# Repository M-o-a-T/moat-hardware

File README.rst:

=============
MoaT Hardware
=============

This is the collection of files for the physical side of MoaT:
Schematics and layouts (kicad), Enclosures (OpenSCAD).

++++++++++++++++
Up-to-date stuff
++++++++++++++++

---
BMS
---

Controller and module for battery management.

The hardware design supports both active-high (diyBMS) and active-low
(MoaT) serial connections.

----
Wire
----

Connect some wires to the MoaT board.

----
misc
----

Random stuff (Enocean adapter, USB intercept, …).

-----
adapt
-----

+++++++++
Old stuff
+++++++++

CPUs
====

The ``proc/`` directory contains CPU boards, i.e. things that have a bus plug.

CPUs are responsible for adapting 1wire (5V) and MoaTbus (12V) to their
internal voltage.

Boards
======

The ``board/`` directory contains everything that has a bus socket, i.e.
interfaces to the Real World.

Many of these boards have 12V-MoaTbus, 5V-1wire, and/or 3.3V-I2C connectors.

The boards are not responsible for translating voltages to the (commonly)
3.3V which CPUs expect.

Breadboard
++++++++++

The most important part. Use this to test CPUs.

Heating
+++++++

This board has two transistors to switch one or two 24V radiator
valves (PPM).

Smoke detector
++++++++++++++

This board fits into a Gira Dual or Q smoke detector.

Old stuff
=========

The ``old/`` directory contains things I need to clean up.

+++++++++
Licensing
+++++++++

(Almost) all files in this archive are (c) 2021-2022 by Matthias Urlichs.
They are licensed under the GNU General Public License, V3.

This means: if you use any these files to build something which you sell or
give to somebody else, you're required to make the schematics, layouts,
design files, and source code of the resulting product available.

Developing these devices takes time and money. Thus, while using all or
part of this achive commercially is OK, their creators hereby humbly ask
for adequate financial remuneration if you use any of these files for
monetary gain. Thank you.

License exception
+++++++++++++++++

The battery module in the bms/cell subdirectory has originally been
designed by Stuart Pittaway. It is governed by a Creative Commons
Attribution-NonCommercial-ShareAlike 2.0 UK: England/Wales license. See the
file ``bms/cell/LICENSE`` for details.

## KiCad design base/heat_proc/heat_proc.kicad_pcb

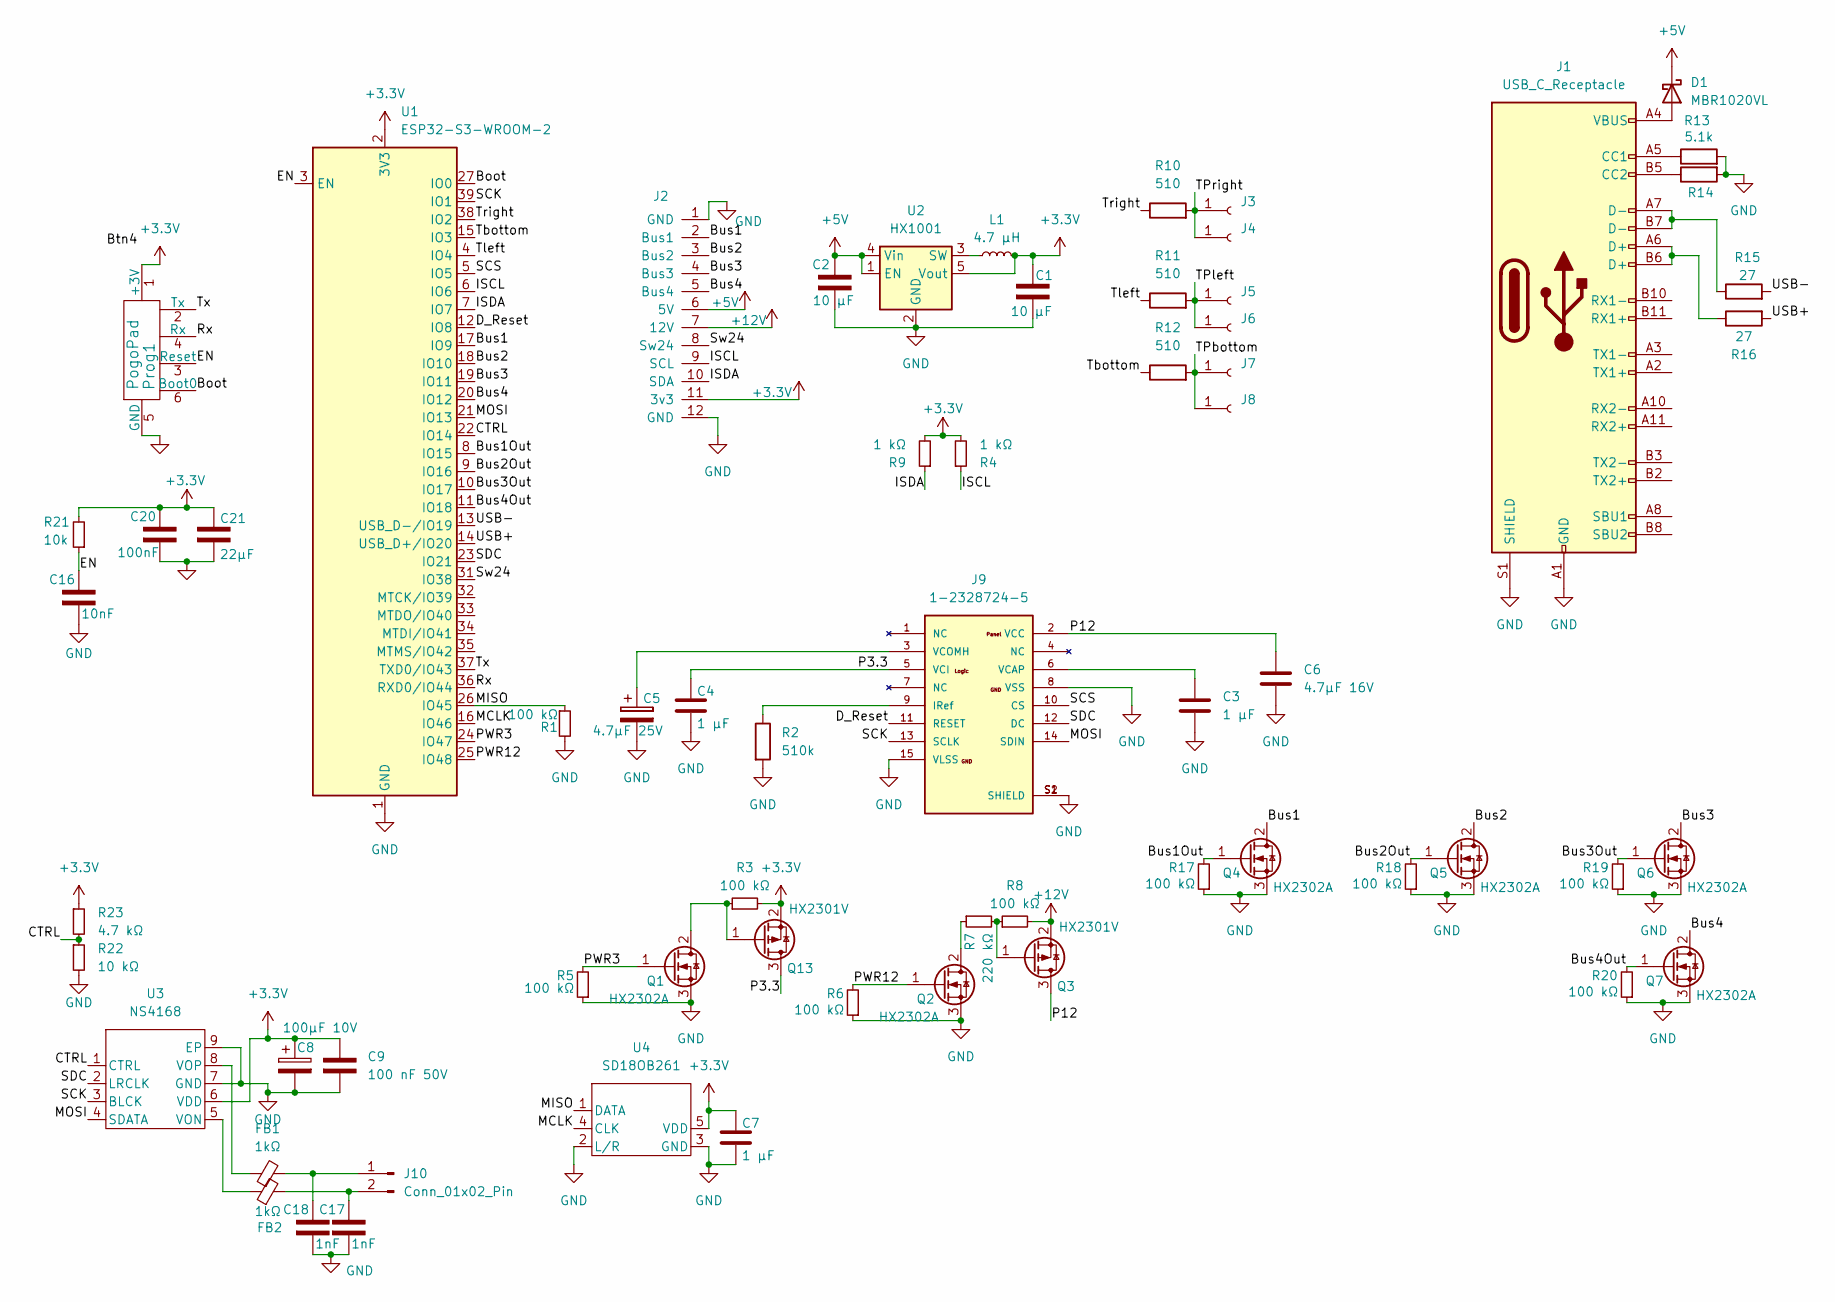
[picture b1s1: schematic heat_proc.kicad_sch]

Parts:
C1, C2: CP_10µ_16V_0603; C_0603_1608Metric; LCSC C108340
C3, C4, C7: C_1µ_25V_0603; C_0603_1608Metric; Farnell 3581460
C5: 4.7µF 25V; C_0603_1608Metric; LCSC C69335
C6: 4.7µF 16V; C_0603_1608Metric; LCSC C69335
C8: CP_100µ_10V; C_1210_3225Metric; Farnell 2326221
C9: CP_100n_50V_0603; C_0603_1608Metric; LCSC C14663
C16: 10nF; C_0603_1608Metric; LCSC C1589
C17, C18: 1nF; C_0603_1608Metric; LCSC C1588
C20: 100nF; C_0402_1005Metric; LCSC C6119799
C21: 22µF; C_1206_3216Metric; LCSC C12891
D1: MBR1020VL; D_SOD-123; LCSC C6299858
FB1, FB2: 1kΩ; L_0805_2012Metric; LCSC C51018431
J1: USB_C_Receptacle; USB_C_Receptacle_GCT_USB4110; LCSC C5143397
J2: Moat_Heat_12; JST_SH_SM12B-SRSS-TB_1x12-1MP_P1.00mm_Horizontal; MPN SM12B-SRSS-TB; LCSC C160411
J3, J4, J5, J6, J7, J8: Conn_01x01_Socket; SolderWire-0.5sqmm_1x01_D0.9mm_OD2.1mm
J9: 1-2328724-5; OLED96; LCSC C2919525
J10: Conn_01x02_Pin; Fuse_1210_3225Metric_Pad1.42x2.65mm_HandSolder
L1: 4.7 µH; L_0603_1608Metric; LCSC C295681
Prog1: PogoPad; 2X3_PAD; LCSC C2685197
Q1, Q2, Q4, Q5, Q6, Q7: HX2302A; SOT-23; LCSC C296295
Q3, Q13: HX2301V; SOT-23; LCSC C7499856
R1, R3, R5, R6, R8, R17, R18, R19, R20: R_100k_0603; R_0603_1608Metric; LCSC C14675
R2: 510k; R_0603_1608Metric; LCSC C23192
R4, R9: R_1k_0603; R_0603_1608Metric; LCSC C21190
R7: R_220k_0603; R_0603_1608Metric; LCSC C22961
R10, R11, R12: 510; R_0603_1608Metric; LCSC C23193
R13, R14: 5.1k; R_0603_1608Metric; LCSC C23186
R15, R16: 27; R_0402_1005Metric; LCSC C321419
R21: 10k; R_0603_1608Metric; LCSC C25804
R22: R_10k_0603; R_0603_1608Metric; LCSC C25804
R23: R_4k7_0603; R_0603_1608Metric; LCSC C25804
U1: ESP32-S3-WROOM-2
U2: HX1001; TSOT-23-5; LCSC C42412961
U3: NS4168; SOIC-8-1EP_3.9x4.9mm_P1.27mm_EP2.41x3.81mm; LCSC C910588
U4: SD18OB261; Knowles_LGA-5_3.5x2.65mm

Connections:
+3.3V: C1.1, C7.1, C8.1, C9.1, C20.1, C21.1, J2.11 (3v3), L1.2, Prog1.1 (+3V), Q13.2 (S), R3.2, R4.2, R9.2, R21.2, R23.1, U1.2 (3V3), U2.5 (Vout), U3.6 (VDD), U4.5 (VDD)
+5V: C2.1, D1.1 (K), J2.6 (5V), U2.1 (EN), U2.4 (Vin)
+12V: J2.7 (12V), Q3.2 (S), R8.2
/Boot: Prog1.6 (Boot0), U1.27 (IO0)
/Bus1: J2.2 (Bus1), Q4.2 (D), U1.17 (IO9)
/Bus1Out: Q4.1 (G), R17.2, U1.8 (IO15)
/Bus2: J2.3 (Bus2), Q5.2 (D), U1.18 (IO10)
/Bus2Out: Q5.1 (G), R18.2, U1.9 (IO16)
/Bus3: J2.4 (Bus3), Q6.2 (D), U1.19 (IO11)
/Bus3Out: Q6.1 (G), R19.2, U1.10 (IO17)
/Bus4: J2.5 (Bus4), Q7.2 (D), U1.20 (IO12)
/Bus4Out: Q7.1 (G), R20.2, U1.11 (IO18)
/CTRL: R22.1, R23.2, U1.22 (IO14), U3.1 (CTRL)
/D_Reset: J9.11 (RESET), U1.12 (IO8)
/EN: C16.1, Prog1.3 (Reset), R21.1, U1.3 (EN)
/ISCL: J2.9 (SCL), R4.1, U1.6 (IO6)
/ISDA: J2.10 (SDA), R9.1, U1.7 (IO7)
/MCLK: U1.16 (IO46), U4.4 (CLK)
/MISO: R1.1, U1.26 (IO45), U4.1 (DATA)
/MOSI: J9.14 (SDIN), U1.21 (IO13), U3.4 (SDATA)
/P3.3: C4.1, J9.5 (VCI), Q13.3 (D)
/P12: C6.1, J9.2 (VCC), Q3.3 (D)
/PWR3: Q1.1 (G), R5.2, U1.24 (IO47)
/PWR12: Q2.1 (G), R6.2, U1.25 (IO48)
/Rx: Prog1.4 (Rx), U1.36 (RXD0/IO44)
/SCK: J9.13 (SCLK), U1.39 (IO1), U3.3 (BLCK)
/SCS: J9.10 (CS), U1.5 (IO5)
/SDC: J9.12 (DC), U1.23 (IO21), U3.2 (LRCLK)
/Sw24: J2.8 (Sw24), U1.31 (IO38)
/TPbottom: J7.1 (Pin_1_1), J8.1 (Pin_1_1), R12.2
/TPleft: J5.1 (Pin_1_1), J6.1 (Pin_1_1), R11.2
/TPright: J3.1 (Pin_1_1), J4.1 (Pin_1_1), R10.2
/Tbottom: R12.1, U1.15 (IO3)
/Tleft: R11.1, U1.4 (IO4)
/Tright: R10.1, U1.38 (IO2)
/Tx: Prog1.2 (Tx), U1.37 (TXD0/IO43)
/USB+: R16.2, U1.14 (USB_D+/IO20)
/USB-: R15.2, U1.13 (USB_D-/IO19)
GND: C1.2, C2.2, C3.2, C4.2, C5.2, C6.2, C7.2, C8.2, C9.2, C16.2, C17.2, C18.2, C20.2, C21.2, J1.A1 (GND), J1.A12 (GND), J1.B1 (GND), J1.B12 (GND), J1.S1 (SHIELD), J2.1 (GND), J2.12 (GND), J9.8 (VSS), J9.15 (VLSS), J9.S1 (SHIELD), J9.S2 (SHIELD), Prog1.5 (GND), Q1.3 (S), Q2.3 (S), Q4.3 (S), Q5.3 (S), Q6.3 (S), Q7.3 (S), R1.2, R2.2, R5.1, R6.1, R13.2, R14.2, R17.1, R18.1, R19.1, R20.1, R22.2, U1.1 (GND), U1.40 (GND), U1.41 (GND), U2.2 (GND), U3.7 (GND), U3.9 (EP), U4.2 (L/R), U4.3 (GND)
unnamed: D1.2 (A), J1.A4 (VBUS), J1.A9 (VBUS), J1.B4 (VBUS), J1.B9 (VBUS)
unnamed: J1.A5 (CC1), R13.1
unnamed: J1.B5 (CC2), R14.1
unnamed: J1.A6 (D+), J1.B6 (D+), R16.1
unnamed: J1.A7 (D-), J1.B7 (D-), R15.1
unnamed: J9.9 (IRef), R2.1
unnamed: C3.1, J9.6 (VCAP)
unnamed: C5.1, J9.3 (VCOMH)
unnamed: C18.1, FB1.2, J10.1
unnamed: C17.1, FB2.2, J10.2
unnamed: Q1.2 (D), Q13.1 (G), R3.1
unnamed: Q2.2 (D), R7.1
unnamed: Q3.1 (G), R7.2, R8.1
unnamed: L1.1, U2.3 (SW)
unnamed: FB2.1, U3.5 (VON)
unnamed: FB1.1, U3.8 (VOP)

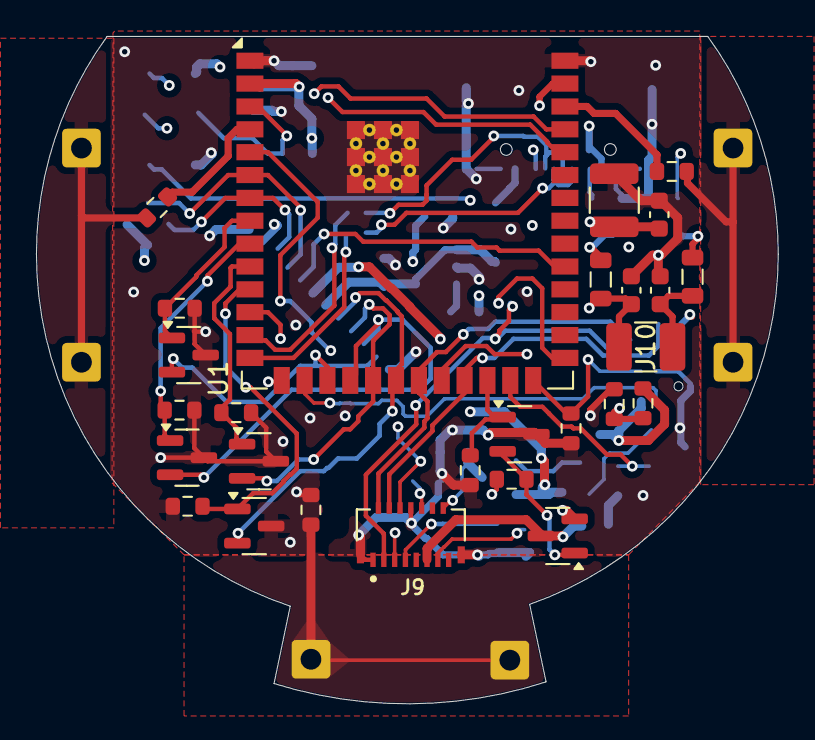
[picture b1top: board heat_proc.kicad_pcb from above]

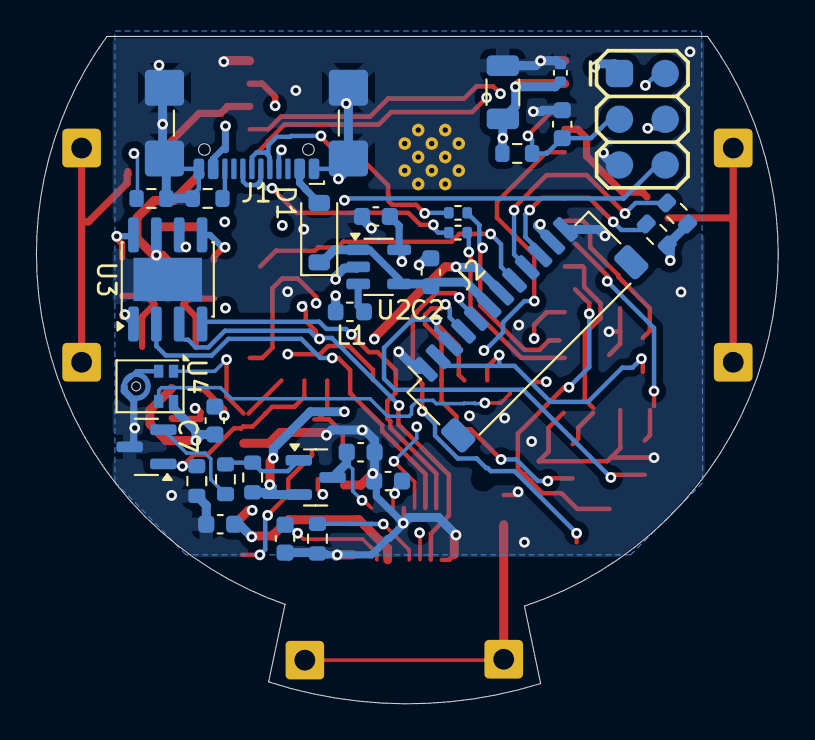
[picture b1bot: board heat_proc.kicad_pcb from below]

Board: 4 copper layers, 41.2 x 37.1 mm, 64 parts (31 on the bottom side), 55 nets.

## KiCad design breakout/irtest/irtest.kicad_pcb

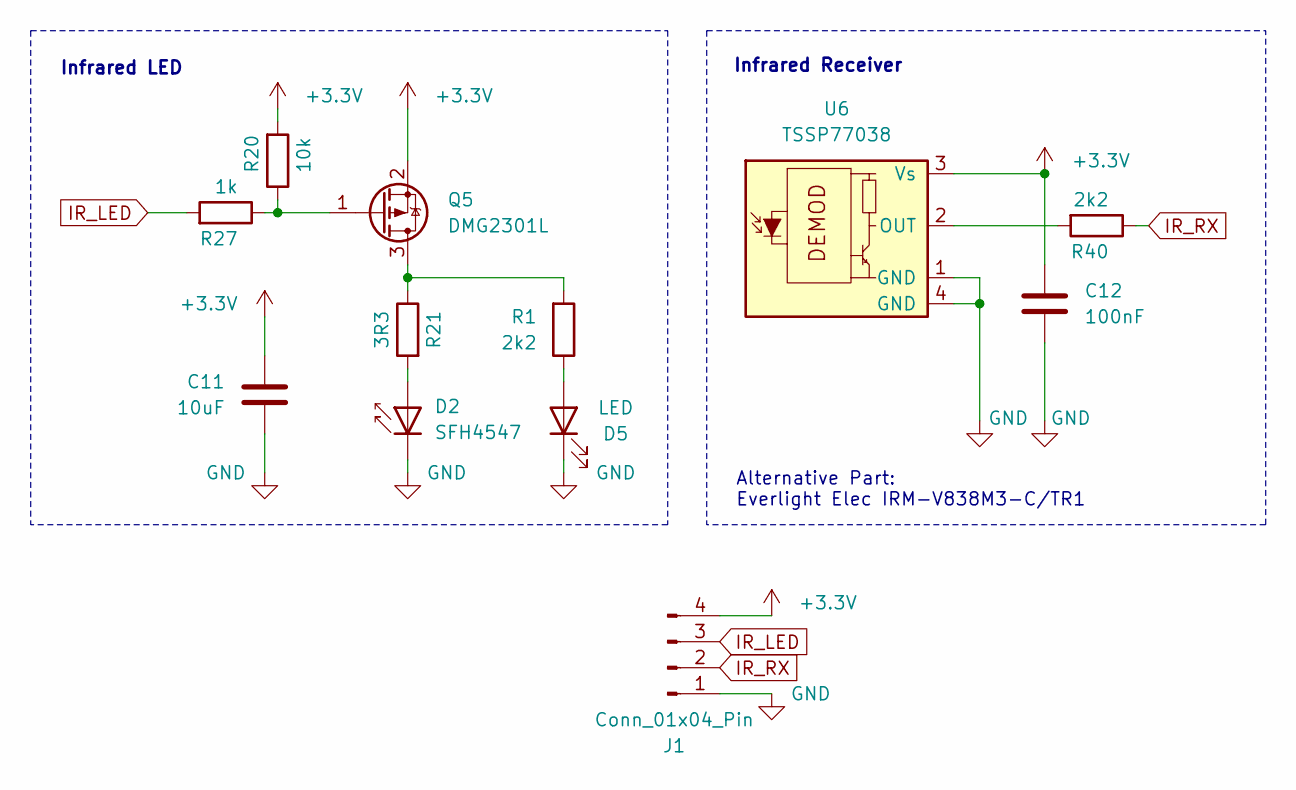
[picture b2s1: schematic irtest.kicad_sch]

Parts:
C11: 10uF; C_0805_2012Metric; LCSC C15850
C12: 100nF; C_0603_1608Metric; LCSC C1591
D2: SFH4547; LED_5mm_Side_Mount; LCSC C405273
D5: LED; LED_0603_1608Metric; LCSC C965807
J1: Conn_01x04_Pin; PinHeader_1x04_P2.54mm_Vertical
Q5: DMG2301L; SOT-23; LCSC C102619
R1, R40: 2k2; R_0603_1608Metric; LCSC C114662
R20: 10k; R_0603_1608Metric; LCSC C98220
R21: 3R3; R_0805_2012Metric; LCSC C16257
R27: 1k; R_0603_1608Metric; LCSC C22548
U6: TSSP77038; Heimdall vertical; LCSC C3291489

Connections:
+3.3V: C11.2, C12.1, J1.4, Q5.2 (S), R20.2, U6.3 (Vs)
GND: C11.1, C12.2, D2.1 (K), D5.1 (K), J1.1, U6.1 (GND), U6.4 (GND)
IR_LED: J1.3, R27.2
IR_RX: J1.2, R40.1
unnamed: D2.2 (A), R21.2
unnamed: D5.2 (A), R1.1
unnamed: Q5.3 (D), R1.2, R21.1
unnamed: Q5.1 (G), R20.1, R27.1
unnamed: R40.2, U6.2 (OUT)

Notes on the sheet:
Alternative Part: Everlight Elec IRM-V838M3-C/TR1
Infrared LED
Infrared Receiver

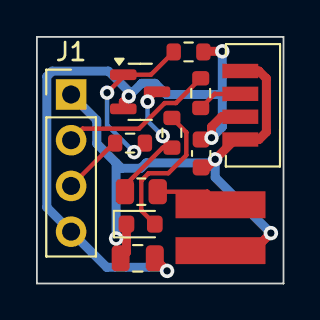
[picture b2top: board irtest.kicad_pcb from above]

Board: 2 copper layers, 13.7 x 13.7 mm, 12 parts (0 on the bottom side), 9 nets.

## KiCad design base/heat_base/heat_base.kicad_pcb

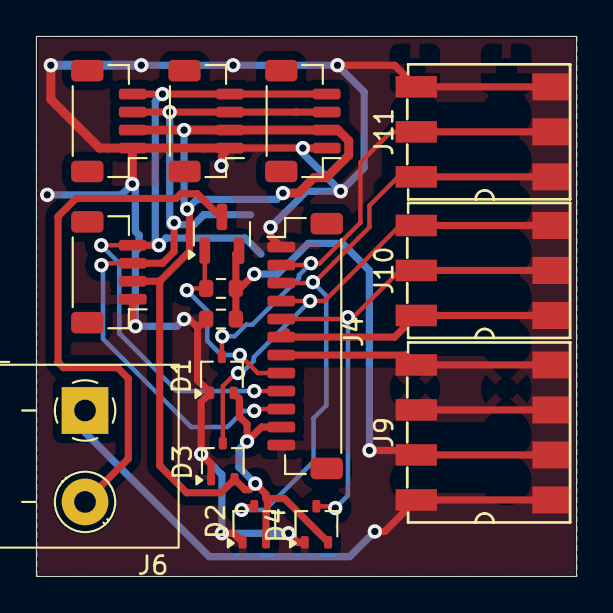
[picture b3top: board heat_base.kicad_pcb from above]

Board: 2 copper layers, 30.0 x 30.0 mm, 16 parts (0 on the bottom side), 14 nets.

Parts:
D1, D2, D3, D4: BAT54SW; SOT-323_SC-70
J1, J2, J3, J7: QwIIC; JST_SH_BM04B-SRSS-TB_1x04-1MP_P1.00mm_Vertical
J4: Moat_Heat_12; JST_SH_BM12B-SRSS-TB_1x12-1MP_P1.00mm_Vertical
J6: Screw; Conn_P5.1mm_2_Molex
J9: Conn_01x04_Socket; AVX_9276_4Pin_HS
J10, J11: Conn_01x03_Socket; AVX_9276_3Pin_HS
Q1: 2N7002; SOT-23
R1: R_1M_0603; R_0603_1608Metric
R2: R_10_0603; R_0603_1608Metric

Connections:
+3.3V: D1.2, D2.2, D3.2, D4.2, J1.2 (3V3), J2.2 (3V3), J3.2 (3V3), J4.11 (3v3), J7.2 (3V3)
/24V: J6.1, J9.1
/Bus1: D1.3, J4.2 (Bus1), J11.2
/Bus2: D2.3, J4.3 (Bus2), J11.1
/Bus3: D3.3, J4.4 (Bus3), J10.3
/Bus4: D4.3, J4.5 (Bus4), J10.2
GND: D1.1, D2.1, D3.1, D4.1, J1.1 (GND), J2.1 (GND), J3.1 (GND), J4.1 (GND), J4.12 (GND), J7.1 (GND), J9.3, J11.3, R2.1
GNDPWR: J9.2, Q1.2 (S), R1.2, R2.2
unnamed: J1.4 (SCL), J2.4 (SCL), J3.4 (SCL), J4.9 (SCL), J7.4 (SCL)
unnamed: J1.3 (SDA), J2.3 (SDA), J3.3 (SDA), J4.10 (SDA), J7.3 (SDA)
unnamed: J4.7 (12V), J9.4
unnamed: J4.8 (Sw24), Q1.1 (G), R1.1
unnamed: J6.2, Q1.3 (D)
unnamed: J4.6 (5V), J10.1

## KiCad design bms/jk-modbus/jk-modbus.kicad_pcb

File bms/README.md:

This directory contains schematics etc. pertaining to our BMS.

== Serial Communications

Instead of isoSPI or similar schemes that require specialized ICs, we use
remote-powered digital isolators. This allows us to combine controllers as
required.

All modules are connected in a loop. Communication can run both ways.
Thus a single interrupted connection or wire will not hurt.

We *always* connect an OUT plug to an IN plug. Damage will result when two
OUT sockets get connected. The same happens with two IN sockets.

== Wire functions

=== GND, V+

Power for communication.

=== RGND, V+R

Reverse power.

=== Tx, RxR

Forward and Reverse comm loops. Their voltage level is that cable's GND/V+.

=== TxR, Rx

Unused (for now).

== Ground levels

There are several possible supply levels.

* Pwr: The module's "natural" power level (e.g. the negative pole of the battery
  it controls, or whatever else something uses as ground reference).

* Pwr-O: forward power supply on the OUT link

* Pwr-I: forward power supply on the IN link

* Pwr-RI: reverse power supply on the IN link

* Pwr-RO: reverse power supply on the OUT link

=== Self-powered modules

Connect Pwr, Pwr-O and Pwr-RI. Pwr-I supplies the digital isolator.
Pwr-RO is left open.

Tx/Rx from IN is connected to an isolator. The signals on OUT are supplied
from internal power.

=== Bus-powered modules

You need two isolated DC/DC converters (one on Pwr-I and one on Pwr-RO).
The module is now powered. Continue as above.

== Non-redundant mode

If you don't care about redundancy – or your controller only has one
available UART – there's no need to interface with the reverse link. The
serial interface on your isolator now intercepts Tx.

Connect Pwr-I to Pwr-O; connect Pwr-RI to Pwr-RO.

= Protection

== Fuses

We want to prevent catastrophic failure (i.e. things going up in smoke and
fire) when somebody happens to mis-plug two modules.

Thus,

* Pwr-O and Pwr-RI get fuses and TVS diodes.

* Pwr-I and PWR-RO, if connected, get TVS diodes.

* All serial links get protected by 100-Ohm resistors and protective
  diodes.

These measures are not sufficient to prevent terminal damage to a module if
you do mis-plug something, but at least there should be no fire.

== High voltages

Normal Cat5 cable is not rated for high voltage differentials, and frankly
neither are the fuses used in th MoaT modules. Thus **always interleave
modules**.

To use a simple example: if you have a controller A, a high-side switch B,
and eight battery modules C D E F G H I K, you do **not** connect them like
A-B-C-D-…-K-A. or A-C-D-…-K-B-A or a similar combination. Instead, you use
something like A-C-E-G-I-B-K-H-F-D-A. This ensures that any two ground levels
are separated by *at most* two battery modules' worth of voltage.

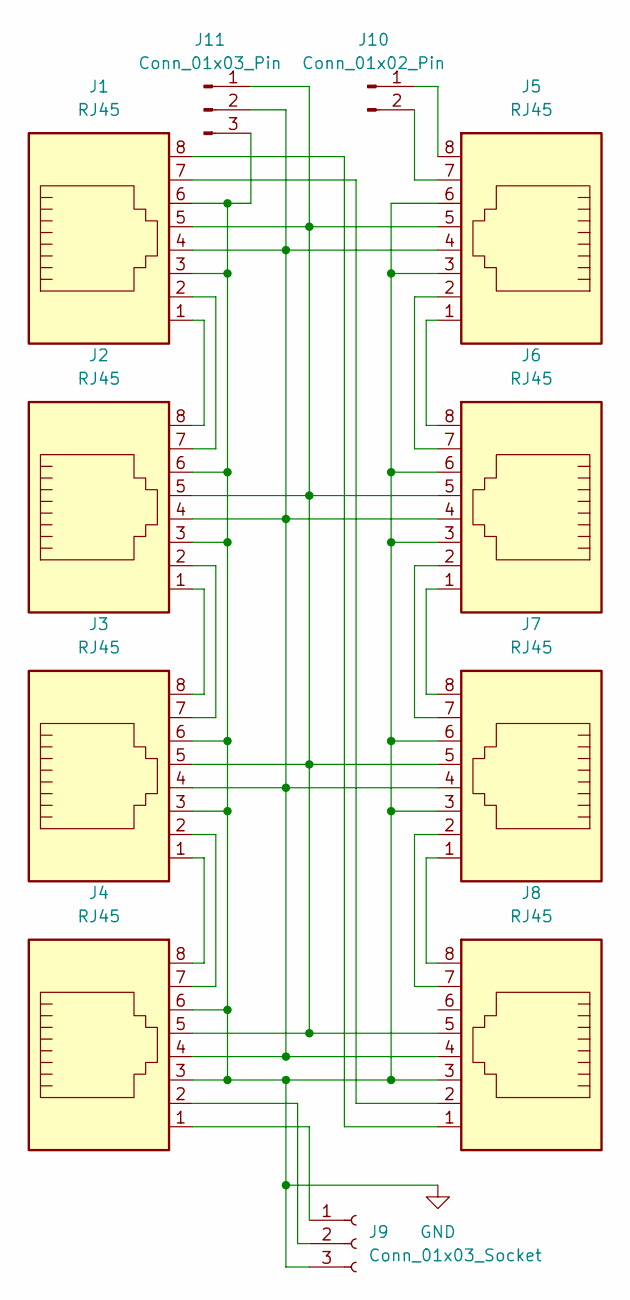
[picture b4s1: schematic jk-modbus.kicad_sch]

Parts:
J1, J2, J3, J4, J5, J6, J7, J8: RJ45; RJ45-NO-SHIELD
J9: Conn_01x03_Socket; 1X03_GN
J10: Conn_01x02_Pin; SolderWire-0.5sqmm_1x02_P4.6mm_D0.9mm_OD2.1mm
J11: Conn_01x03_Pin; SolderWire-0.5sqmm_1x03_P4.6mm_D0.9mm_OD2.1mm

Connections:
GND: J1.3, J1.6, J2.3, J2.6, J3.3, J3.6, J4.3, J4.6, J5.3, J5.6, J6.3, J6.6, J7.3, J7.6, J8.3, J9.3, J11.3
unnamed: J1.1, J2.8
unnamed: J1.2, J2.7
unnamed: J1.7, J8.2
unnamed: J1.8, J8.1
unnamed: J2.1, J3.8
unnamed: J2.2, J3.7
unnamed: J3.1, J4.8
unnamed: J3.2, J4.7
unnamed: J5.1, J6.8
unnamed: J5.2, J6.7
unnamed: J6.1, J7.8
unnamed: J6.2, J7.7
unnamed: J7.1, J8.8
unnamed: J7.2, J8.7
unnamed: J4.1, J9.1
unnamed: J4.2, J9.2
unnamed: J5.8, J10.1
unnamed: J5.7, J10.2
unnamed: J1.5, J2.5, J3.5, J4.5, J5.5, J6.5, J7.5, J8.5, J11.1
unnamed: J1.4, J2.4, J3.4, J4.4, J5.4, J6.4, J7.4, J8.4, J11.2

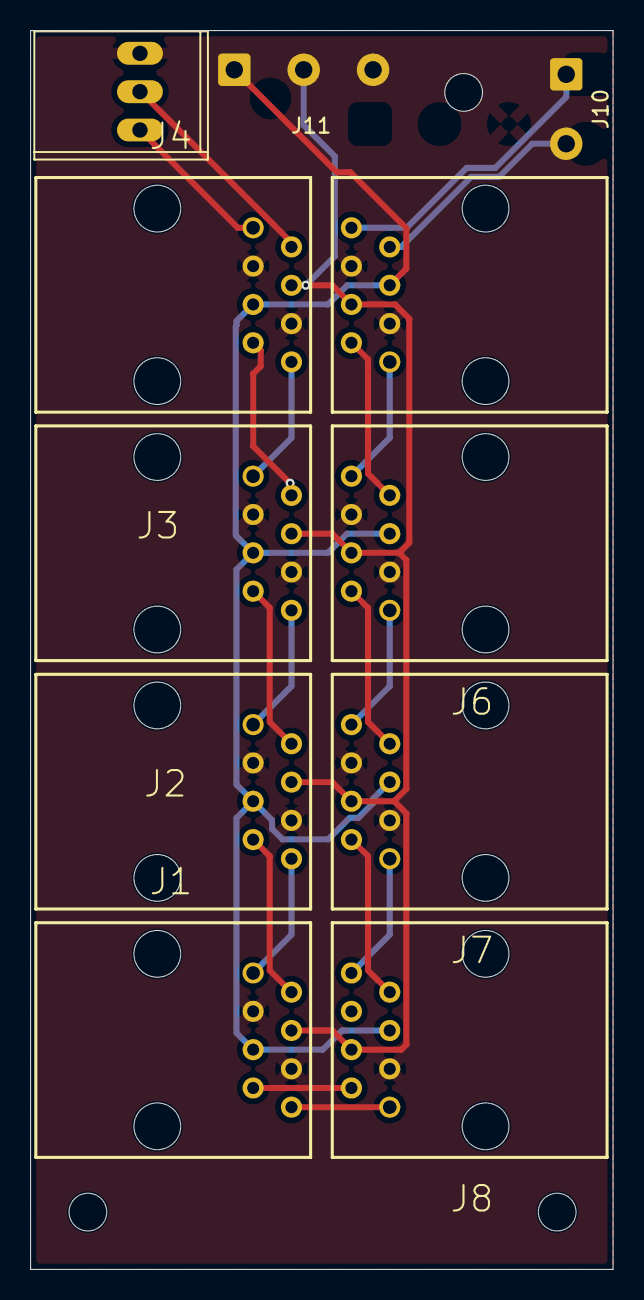
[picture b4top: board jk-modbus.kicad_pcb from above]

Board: 2 copper layers, 38.6 x 82.1 mm, 11 parts (0 on the bottom side), 21 nets.

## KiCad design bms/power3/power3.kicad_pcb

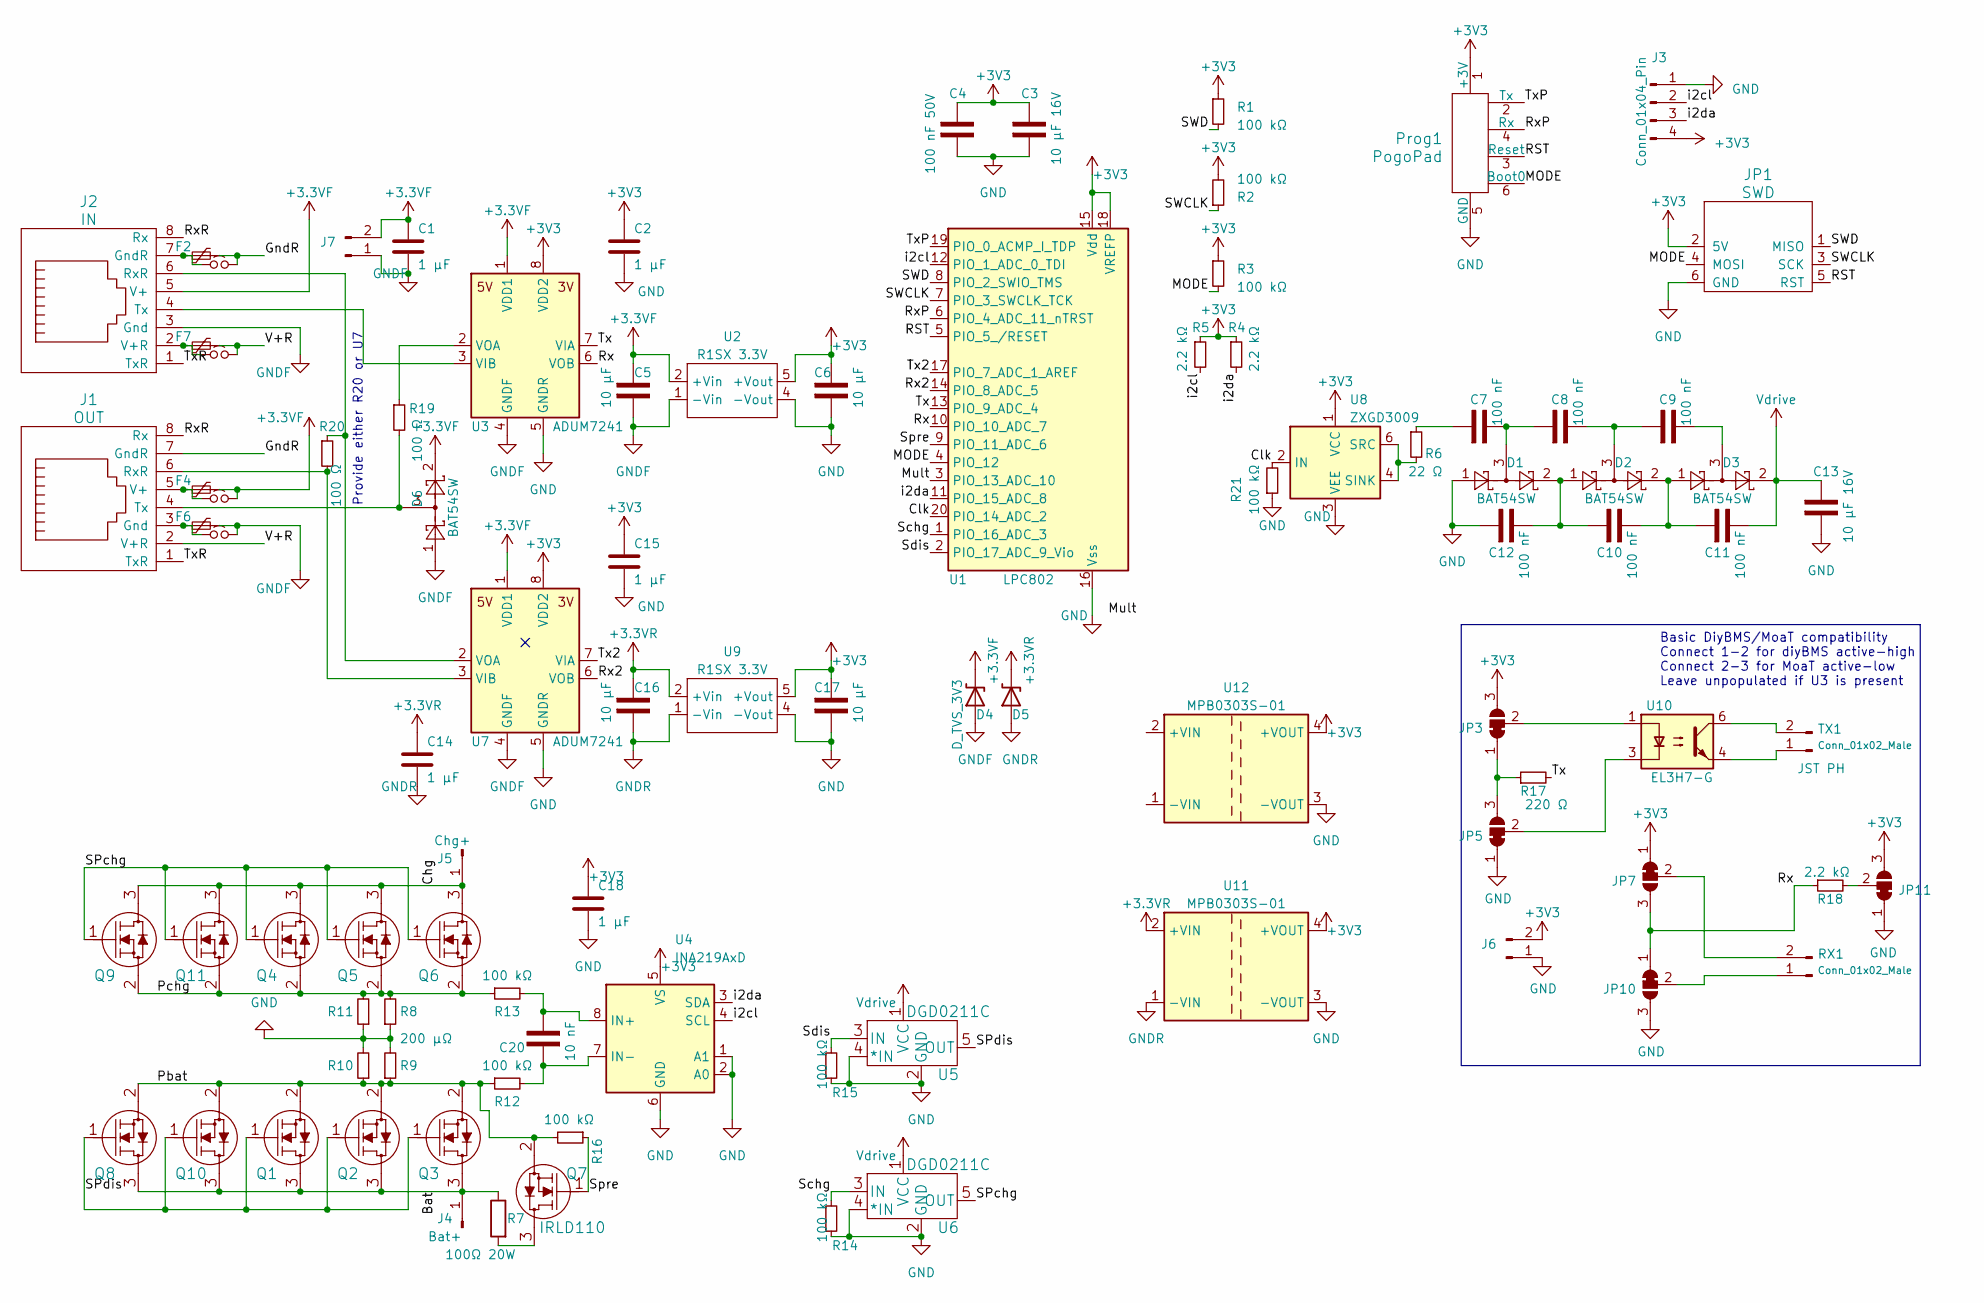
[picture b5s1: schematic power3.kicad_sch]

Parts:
C1, C2, C14, C15, C18: CP_1µ_10V_0603; R_0603_HandSolder; Farnell 3013419
C3, C5, C6, C13, C16, C17: CP_10µ_16V_0603; R_0603_HandSolder
C4, C7, C8, C9, C10, C11, C12: CP_100n_50V_0603; R_0603_HandSolder; LCSC C14663
C20: C_10n_0603; R_0603_HandSolder
D1, D2, D3, D6: BAT54SW; SOT-23
D4: D_TVS_3V3; SOD-123FL; Farnell 1749296
D5: D_TVS_70V; SOD-123FL; Farnell 1749296
F2, F4, F6, F7: T0602 fuse 500mA; R_0603_HandSolder
J1: OUT; RJ45-NO-SHIELD
J2: IN; RJ45-NO-SHIELD
J3: Conn_01x04_Pin; PinSocket_1x04_P2.54mm_Vertical
J4: Bat+; MountingHole_6.4mm_M6_Pad_Via
J5: Chg+; MountingHole_6.4mm_M6_Pad_Via
J6, J7: Conn_01x02_Pin; PinHeader_1x02_P2.54mm_Vertical
JP1: SWD; PinHeader_2x03_P2.54mm_Vertical
JP3, JP5, JP7, JP10, JP11: SolderJumper_3_Bridged12; SolderJumper-3_P1.3mm_Open_Pad1.0x1.5mm
JP4, JP6, JP8, JP9: Jumper_2_Bridged; SolderJumper-2_P1.3mm_Open_TrianglePad1.0x1.5mm
Prog1: PogoPad; 2X3-NS
Q1, Q2, Q3, Q4, Q5, Q6, Q8, Q9, Q10, Q11: IPF016N10NF2SATMA1; IPF016
Q7: IRLD110; HVMDIP IRLD024
R1, R2, R3, R12, R13, R14, R15, R16, R21: R_100k_0603; R_0603_HandSolder
R4, R5, R18: R_2k2_0603; R_0603_HandSolder
R6: R_22_0603; R_0603_HandSolder
R7: 100Ω 20W; R_Axial_Power_L25.0mm_W9.0mm_P7.62mm_Vertical; Farnell 3951837
R8, R9, R10, R11: R_0m2_Yaego; PU5931
R17: R_220_0603; R_0603_HandSolder; PartNumber 0805W8F2200T5E; LCSC C17557
R19, R20: R_100_0603; R_0603_HandSolder
RX1: Conn_01x02_Male; JST_PH_S2B-PH-K_1x02_P2.00mm_Horizontal; PartNumber S2B-PH-K(LF)(SN); LCSCStockCode C265016
TX1: Conn_01x02_Male; JST_PH_S2B-PH-K_1x02_P2.00mm_Horizontal; PartNumber S2B-PH-K(LF)(SN); LCSC C265016
U1: LPC802; TSSOP-20_4.4x5mm_P0.5mm
U2, U9: R1SX 3.3V; R1SX
U3, U7: ADUM7241; SOIC-8_3.9x4.9mm_P1.27mm
U4: INA219AxD; SOIC-8_3.9x4.9mm_P1.27mm; LCSC C138706
U5, U6: DGD0211C; TSOT-23-5
U8: ZXGD3009; SOT-23-6
U10: PC817; MFSOP6-4_4.4x3.6mm_P1.27mm; Farnell 3397435
U11, U12: MPB0303S-01; Converter_DCDC_Murata_CRE1xxxxxx3C_THT

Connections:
+3V3: C2.1, C3.1, C4.1, C6.1, C15.1, C17.1, C18.1, J3.4, J6.2, JP1.2 (5V), JP3.3 (B), JP7.1 (A), JP11.3 (B), Prog1.1 (+3V), R1.1, R2.2, R3.1, R4.1, R5.1, U1.15 (Vdd), U1.18 (VREFP), U2.5 (+Vout), U3.8 (VDD2), U4.5 (VS), U7.8 (VDD2), U8.1 (VCC), U9.5 (+Vout), U11.4 (+VOUT), U12.4 (+VOUT)
/Bat: J4.1, Q1.3 (DRAIN), Q2.3 (DRAIN), Q3.3 (DRAIN), Q8.3 (DRAIN), Q10.3 (DRAIN), R7.1
/Chg: J5.1, Q4.3 (DRAIN), Q5.3 (DRAIN), Q6.3 (DRAIN), Q9.3 (DRAIN), Q11.3 (DRAIN)
/Clk: R21.2, U1.20 (PIO_14_ADC_2), U8.2 (IN)
/GndR: F2.2, J1.7 (GndR), JP4.1 (A)
/MODE: JP1.4 (MOSI), Prog1.6 (Boot0), R3.2, U1.4 (PIO_12)
/Mult: U1.3 (PIO_13_ADC_10)
/Pbat: Q1.2 (SOURCE), Q2.2 (SOURCE), Q3.2 (SOURCE), Q7.2 (SOURCE), Q8.2 (SOURCE), Q10.2 (SOURCE), R9.1, R10.1, R12.1, R16.2
/Pchg: Q4.2 (SOURCE), Q5.2 (SOURCE), Q6.2 (SOURCE), Q9.2 (SOURCE), Q11.2 (SOURCE), R8.2, R11.2, R13.1
/RST: JP1.5 (RST), Prog1.3 (Reset), U1.5 (PIO_5_/RESET)
/Rx: JP7.3 (B), JP10.1 (A), R18.1, U1.10 (PIO_10_ADC_7), U3.6 (VOB)
/Rx2: U1.14 (PIO_8_ADC_5), U7.6 (VOB)
/RxP: Prog1.4 (Rx), U1.6 (PIO_4_ADC_11_nTRST)
/RxR: J1.8 (Rx), J2.8 (Rx)
/SPchg: Q4.1 (GATE), Q5.1 (GATE), Q6.1 (GATE), Q9.1 (GATE), Q11.1 (GATE), U6.5 (OUT)
/SPdis: Q1.1 (GATE), Q2.1 (GATE), Q3.1 (GATE), Q8.1 (GATE), Q10.1 (GATE), U5.5 (OUT)
/SWCLK: JP1.3 (SCK), R2.1, U1.7 (PIO_3_SWCLK_TCK)
/SWD: JP1.1 (MISO), R1.2, U1.8 (PIO_2_SWIO_TMS)
/Schg: R14.2, U1.1 (PIO_16_ADC_3), U6.3 (IN)
/Sdis: R15.2, U1.2 (PIO_17_ADC_9_Vio), U5.3 (IN)
/Spre: Q7.1 (GATE), R16.1, U1.9 (PIO_11_ADC_6)
/Tx: R17.2, U1.13 (PIO_9_ADC_4), U3.7 (VIA)
/Tx2: U1.17 (PIO_7_ADC_1_AREF), U7.7 (VIA)
/TxP: Prog1.2 (Tx), U1.19 (PIO_0_ACMP_I_TDP)
/TxR: J1.1 (TxR), J2.1 (TxR)
/V+R: F7.2, J1.2 (V+R), JP9.1 (A)
/i2cl: J3.2, R5.2, U1.12 (PIO_1_ADC_0_TDI), U4.4 (SCL)
/i2da: J3.3, R4.2, U1.11 (PIO_15_ADC_8), U4.3 (SDA)
GND: C2.2, C3.2, C4.2, C6.2, C12.1, C13.2, C15.2, C17.2, C18.2, D1.1, J3.1, J6.1, JP1.6 (GND), JP5.1 (A), JP10.3 (B), JP11.1 (A), Prog1.5 (GND), R8.1, R9.2, R10.2, R11.1, R14.1, R15.1, R21.1, U1.16 (Vss), U2.4 (-Vout), U3.5 (GNDR), U4.1 (A1), U4.2 (A0), U4.6 (GND), U5.2 (GND), U5.4 (*IN), U6.2 (GND), U6.4 (*IN), U7.5 (GNDR), U8.3 (VEE), U9.4 (-Vout), U11.3 (-VOUT), U12.3 (-VOUT)
unnamed: C7.1, R6.1
unnamed: C7.2, C8.1, D1.3
unnamed: C8.2, C9.1, D2.3
unnamed: C9.2, D3.3
unnamed: C10.1, C12.2, D1.2, D2.1
unnamed: C10.2, C11.1, D2.2, D3.1
unnamed: F6.1, J1.3 (Gnd), JP8.2 (B)
unnamed: J1.6 (RxR), R20.2, U7.3 (VIB)
unnamed: D6.3, J1.4 (Tx), R19.2
unnamed: F4.1, J1.5 (V+), JP6.2 (B)
unnamed: F2.1, J2.7 (GndR), JP4.2 (B)
unnamed: J2.6 (RxR), R20.1, U7.2 (VOA)
unnamed: J2.4 (Tx), U3.3 (VIB)
unnamed: F7.1, J2.2 (V+R), JP9.2 (B)
unnamed: JP3.1 (A), JP5.3 (B), R17.1
unnamed: JP3.2 (C), U10.1
unnamed: JP5.2 (C), U10.3
unnamed: JP7.2 (C), RX1.2
unnamed: JP10.2 (C), RX1.1
unnamed: JP11.2 (C), R18.2
unnamed: Q7.3 (DRAIN), R7.2
unnamed: TX1.1, U10.4
unnamed: TX1.2, U10.6
unnamed: R19.1, U3.2 (VOA)
unnamed: C20.2, R13.2, U4.8 (IN+)
unnamed: C20.1, R12.2, U4.7 (IN-)
unnamed: R6.2, U8.4 (SINK), U8.6 (SRC)
Vdrive: C11.2, C13.1, D3.2, U5.1 (VCC), U6.1 (VCC)

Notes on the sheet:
Basic DiyBMS/MoaT compatibility Connect 1-2 for diyBMS active-high Connect 2-3 for MoaT active-low Leave unpopulated if U3 is present
Provide either R20 or U7

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
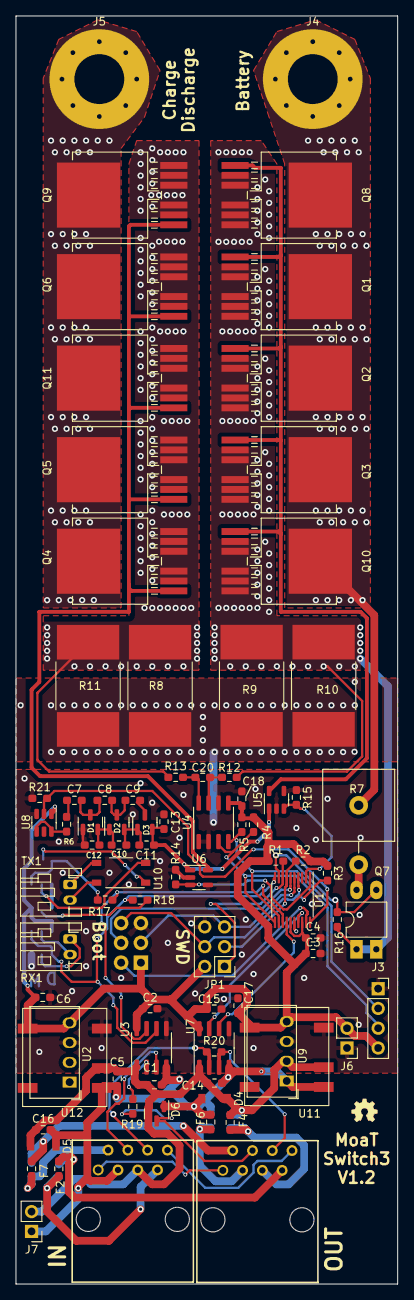
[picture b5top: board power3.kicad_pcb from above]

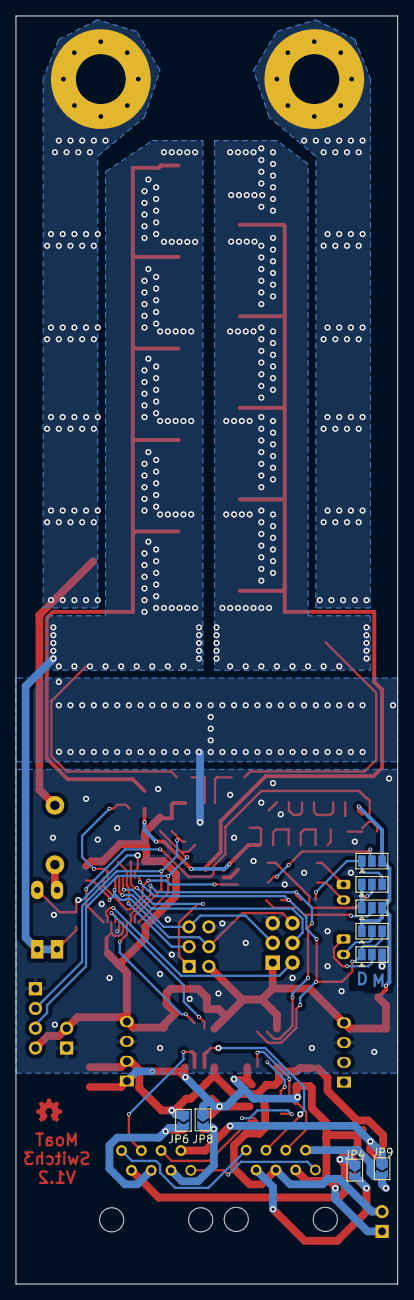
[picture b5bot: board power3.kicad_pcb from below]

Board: 2 copper layers, 49.0 x 162.8 mm, 93 parts (9 on the bottom side), 58 nets.

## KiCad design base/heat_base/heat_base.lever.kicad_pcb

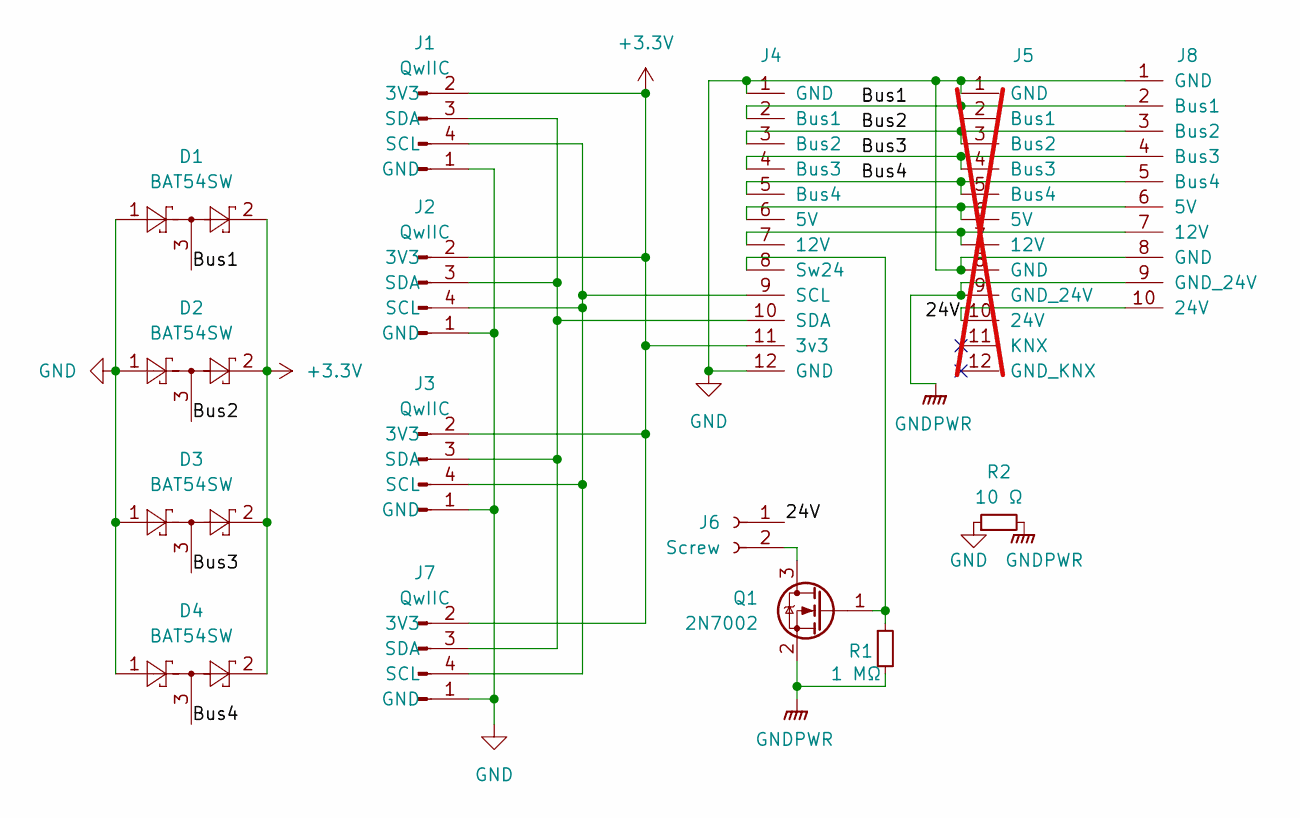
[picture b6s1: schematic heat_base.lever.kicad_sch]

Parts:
D1, D2, D3, D4: BAT54SW; SOT-323_SC-70
J1, J2, J3, J7: QwIIC; JST_SH_BM04B-SRSS-TB_1x04-1MP_P1.00mm_Vertical; LCSC C160390
J4: Moat_Heat_12; JST_SH_BM12B-SRSS-TB_1x12-1MP_P1.00mm_Vertical; MPN BM12B-SRSS-TB(LF)(SN); LCSC C160398
J5: Moat_Bus_12; MoaT_12_Pin_V; MfgrPart GBEC202-0679B001C1AF; Farnell 2783995; not fitted
J6: Screw; Conn_P5.1mm_2_Molex
J8: Moat_Plug_10; P1x10 KF141V 2.54mm; MfgrPart KF141V-2.54 10p; LCSC C475122
Q1: 2N7002; SOT-23
R1: R_1M_0603; R_0603_1608Metric; LCSC C22935
R2: R_10_0603; R_0603_1608Metric; LCSC C22859

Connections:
+3.3V: D1.2, D2.2, D3.2, D4.2, J1.2 (3V3), J2.2 (3V3), J3.2 (3V3), J4.11 (3v3), J7.2 (3V3)
/24V: J5.10 (24V), J6.1, J8.10 (24V)
/Bus1: D1.3, J4.2 (Bus1), J5.2 (Bus1), J8.2 (Bus1)
/Bus2: D2.3, J4.3 (Bus2), J5.3 (Bus2), J8.3 (Bus2)
/Bus3: D3.3, J4.4 (Bus3), J5.4 (Bus3), J8.4 (Bus3)
/Bus4: D4.3, J4.5 (Bus4), J5.5 (Bus4), J8.5 (Bus4)
GND: D1.1, D2.1, D3.1, D4.1, J1.1 (GND), J2.1 (GND), J3.1 (GND), J4.1 (GND), J4.12 (GND), J5.1 (GND), J5.8 (GND), J7.1 (GND), J8.1 (GND), J8.8 (GND), R2.1
GNDPWR: J5.9 (GND_24V), J8.9 (GND_24V), Q1.2 (S), R1.2, R2.2
unnamed: J1.4 (SCL), J2.4 (SCL), J3.4 (SCL), J4.9 (SCL), J7.4 (SCL)
unnamed: J1.3 (SDA), J2.3 (SDA), J3.3 (SDA), J4.10 (SDA), J7.3 (SDA)
unnamed: J4.6 (5V), J5.6 (5V), J8.6 (5V)
unnamed: J4.7 (12V), J5.7 (12V), J8.7 (12V)
unnamed: J4.8 (Sw24), Q1.1 (G), R1.1
unnamed: J6.2, Q1.3 (D)

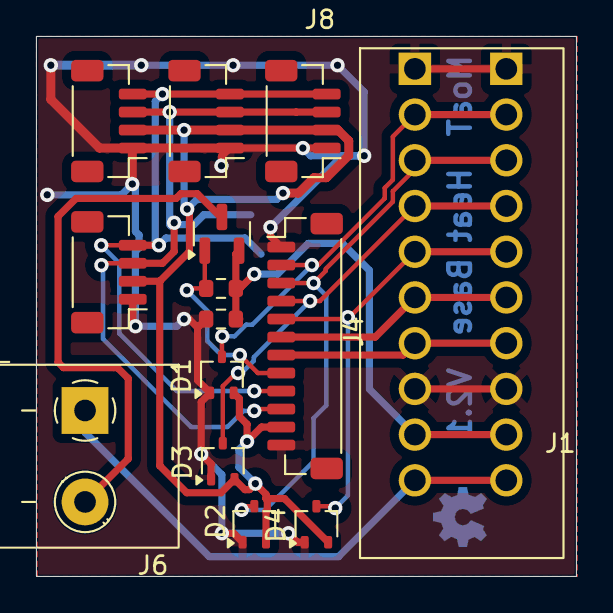
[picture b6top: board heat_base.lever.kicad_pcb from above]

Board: 2 copper layers, 30.0 x 30.0 mm, 14 parts (0 on the bottom side), 14 nets.
